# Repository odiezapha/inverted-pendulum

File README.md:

# Reaction Wheel Stabilized Inverted Pendulum
An inverted pendulum that maintains an upright attitude via reaction wheels. This repository
contains hardware and software development files. See the pdf for system equations.

Renderings:<br />

Simulation output:<br />
<br />

**Sim Test Conditions**<br />
Software: Python 3.6.4 on macOS High Sierra<br />
Computer: MacBook (Retina, 12-inch, Early 2015)<br />
Processor: 1.1 GHz Intel Core M<br />
RAM: 8 GB 1600 MHz DDR3<br />

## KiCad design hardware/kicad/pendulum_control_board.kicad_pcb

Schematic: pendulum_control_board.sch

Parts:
BT1, BT2: 1048; BAT_1048
C1, C4, C5, C7, C8, C10, C11, C12, C13, C14, C15, C16, C18, C19, C20, C21, C22, C23, C25, C26, C37, C41, C43, C47, C56, C64, C65, C66, C71, C72, C74, C75, C79, C82: 0.1uF; SPARKFUN-CAPACITORS_0603
C2, C57, C58, C59, C60, C61, C62, C63, C67, C68, C69, C70: 1.0uF; SPARKFUN-CAPACITORS_0603
C3, C6: 10uF; SPARKFUN-CAPACITORS_0603
C9, C28, C31, C32, C35: 10nF; SPARKFUN-CAPACITORS_0603
C17, C24, C49, C53: 1uF; SPARKFUN-CAPACITORS_0603
C27: 10uF; SPARKFUN-CAPACITORS_0805
C29, C33: 1nF; SPARKFUN-CAPACITORS_0603
C30, C34, C40, C46: 33nF; SPARKFUN-CAPACITORS_0603
C36, C39, C42, C45: 100uF; C_1206
C38, C44: 5.6nF; SPARKFUN-CAPACITORS_0603
C48, C51, C52, C55: 4.7uF; SPARKFUN-CAPACITORS_0603
C50, C54: 47nF; SPARKFUN-CAPACITORS_0603
C73, C76: 1.0uF; SPARKFUN-CAPACITORS_0805
C77: 10uF; SPARKFUN-CAPACITORS_1210
C78: 2.2uF; SPARKFUN-CAPACITORS_0603
C80, C81: 4.7pF; SPARKFUN-CAPACITORS_0603
D1, D17: MBR0520; SOD-123
D2: BAT54C; DIODE_SOT23
D3, D4, D16: 5973311402; SPARKFUN-LED_LED-1206
D5, D6: Yellow; SPARKFUN-LED_LED-0603
D7, D8, D9, D10: 15V; SPARKFUN-DISCRETESEMI_PANASONIC_SMINI2-F5-B
D11, D12, D13, D14: 1N4148; SOD-123
D15: QBLP677-RGB; SPARKFUN-LED_P-LCC-4-3
FB1, FB2, FB3: 30~/1.8A; SPARKFUN-COILS_0603
IC1: STM32F411CEU6; MICRO-STM_V3_UFQFPN48
IC2: LM358D; LINEAR_SO08
J1: DX07S024JJ2; TRISTAN+ROBITAILLE'S+LIBRARY_DX07S0224JJ2_USB-C
L1, L2: MSS1038-153ML; INDUCTOR-COILCRAFT_MSS1038
PAD1: T1-; WIREPAD_1_6_0_8
PAD2: T2-; WIREPAD_1_6_0_8
PAD3: T3-; WIREPAD_1_6_0_8
PAD4: T4-; WIREPAD_1_6_0_8
PAD5: T1+; WIREPAD_1_6_0_8
PAD6: T2+; WIREPAD_1_6_0_8
PAD7: T3+; WIREPAD_1_6_0_8
PAD8: T4+; WIREPAD_1_6_0_8
Q1, Q2, Q3, Q4: BSS138; BSS138_10_SOT23
Q5, Q6, Q7: 2N7002; TRANSISTOR-FET_SOT23
R1: 900K; SPARKFUN-RESISTORS_0603
R2, R5, R6, R9, R50, R63: 4.7K; SPARKFUN-RESISTORS_0603
R3, R4: 200K; SPARKFUN-RESISTORS_0603
R7, R8: 470; SPARKFUN-RESISTORS_0603
R10, R15, R17, R21, R25, R27, R28, R29, R30, R31, R34, R35, R38, R48, R66, R76, R89, R91, R102, R106: 10K; SPARKFUN-RESISTORS_0603
R11, R12, R13, R14, R19, R20, R23, R24: 68; SPARKFUN-RESISTORS_0603
R16, R18, R22, R26, R46, R100, R101: DNP; SPARKFUN-RESISTORS_0603
R32, R33, R36, R37, R51, R59, R64, R67, R70: 1K; SPARKFUN-RESISTORS_0603
R39, R52: 47K; SPARKFUN-RESISTORS_0603
R40, R53: 33K; SPARKFUN-RESISTORS_0603
R41, R54: 100; SPARKFUN-RESISTORS_0603
R42, R55, R61: 1.8K; SPARKFUN-RESISTORS_0603
R43, R56: 5.6K; SPARKFUN-RESISTORS_0603
R44, R57, R93, R94, R95, R96, R105: 100K; SPARKFUN-RESISTORS_0603
R45, R58: 0.3; SPARKFUN-RESISTORS_0603
R47, R65: 187K; SPARKFUN-RESISTORS_0603
R49, R62: 1M; SPARKFUN-RESISTORS_0603
R60, R68: 80; SPARKFUN-RESISTORS_0603
R69, R71, R73: 3K; SPARKFUN-RESISTORS_0603
R72: 140; SPARKFUN-RESISTORS_0603
R74: 4.5K; SPARKFUN-RESISTORS_0603
R75: 4.7; SPARKFUN-RESISTORS_0603
R77, R90, R92: 220; SPARKFUN-RESISTORS_0603
R78: 402K; SPARKFUN-RESISTORS_0603
R79: 107K; SPARKFUN-RESISTORS_0603
R80: SPARKFUN-RESISTORS_0603
R81, R82, R86, R87: 1; SPARKFUN-RESISTORS_0603
R83, R103, R104: 0; SPARKFUN-RESISTORS_0603
R84: 2K; SPARKFUN-RESISTORS_0603
R85: 115K; SPARKFUN-RESISTORS_0603
R88: 0.01; SPARKFUN-RESISTORS_0603
R97: 330; SPARKFUN-RESISTORS_0603
R98: 20; SPARKFUN-RESISTORS_0603
R99: 1m; R_1206
S1, S2: SPARKFUN-SWITCHES_SWITCH_SPST_SMD_A
S3: SW-SPST; SPARKFUN-SWITCHES_TACTILE_SWITCH_SMD_5.2MM
TP1, TP2, TP3, TP4, TP7: TP-040; KEYSTONE_TP-040
TP5, TP6: TP-040; SolderWirePad_single_2mmDrill
U1: FT231XS; SPARKFUN-IC-COMMS_SSOP20_L
U2, U3: V_REG_317SMD; SPARKFUN-IC-POWER_SOT223
U5: LTC6102DD; LINEAR-TECHNOLOGY_DFN8-3X3
U$1, U$7: L6235; L6234_SO24W
U$2, U$11: TPS61175; LIS3DE_HTSSOP14PWP
U$3: LIS3DE; LIS3DE_LGA-16
U$4: L3GD20H; LIS3DE_LGA-16
U$5: AD7280A; LIS3DE_LQFP48_N
U$6: TUSB320LAI; LIS3DE_X2QFN-12
U$8: ITS13FV2SR; LIS3DE_ITS13FV2SR
U$9, U$13: SS3P6L; LIS3DE_TO-277A
U$10: ISL9238; LIS3DE_TQFN-32
U$12: WE-SD; LIS3DE_ROD-CORE-CHOKE
U$14, U$15, U$16, U$17: EPC2023; LIS3DE_EPC2023
U$18: SI7655DN; LIS3DE_POWERPAK-1212-8S
X1, X2: 5566-8; CON-MOLEX_5566-8
Y2: 32.768kHz; SPARKFUN-CLOCKS_CRYSTAL-SMD-3.2X1.5MM

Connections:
/3P3V: C3.2, C4.2, C5.2, C6.2, C8.1, C10.2, C57.1, C72.2, C73.1, D5.A, D6.A, IC1.9 (VDDA), IC1.24 (VDD), IC1.36 (VDD), IC1.48 (VDD), R3.1, R4.2, R5.2, R6.2, R61.2, R72.1, R76.2, R77.2, R89.2, R90.2, R91.2, R92.2, R93.2, R95.2, R106.2, TP5.1, U1.3 (VCCIO), U1.13 (3V3OUT), U2.2 (OUT), U$3.1 (VDD_IO), U$3.14 (VDD), U$4.1 (VDD_IO), U$4.16 (VDD), U$5.29 (VDRIVE), U$6.12 (VDD)
/5V: C2.1, C74.1, IC2.8 (V+), R70.2, TP6.1, U3.2 (OUT), U5.3 (V-/EN), U5.7 (V+), X1.3, X2.3
/ACOK: Q5.1 (G), R76.1, U$10.24 (ACOK)
/ALERT_BATT: IC1.40 (PB4), U$5.27 (ALERT)
/AUX_TERM: R102.2, U$5.32 (AUX_TERM)
/BATGONE: S2.2, U$10.25 (BATGONE)
/BOOT0: IC1.44 (BOOT0), R105.2, TP7.1
/BRAKE_X: IC1.45 (PB8), U$1.14 (BRAKE)
/BRAKE_Y: IC1.12 (PA2), U$7.14 (BRAKE)
/CB1: R15.1, U$5.12 (CB1)
/CB2: R17.1, U$5.10 (CB2)
/CB3: R21.1, U$5.8 (CB3)
/CB4: R25.1, U$5.6 (CB4)
/CC1: J1.A5 (CC1), U$6.1 (CC1)
/CC2: J1.B5 (CC2), U$6.2 (CC2)
/CLK: IC1.25 (PB12), U$3.4 (SCL/SPC), U$4.2 (SCL/SPC), U$5.22 (SCLK)
/CREF: C25.1, U$5.39 (CREF)
/CSON: C68.2, C69.1, R87.1, U$10.1 (CSON)
/CSOP: C68.1, C70.1, R86.1, U$10.2 (CSOP)
/CS_ACCEL: IC1.15 (PA5), U$3.8 (CS)
/CS_BATT: IC1.29 (PA8), U$5.21 (CS)
/CS_GYRO: IC1.21 (PB10), U$4.5 (CS)
/DEN_GYRO: IC1.18 (PB0), U$4.8 (DEN)
/DM: J1.A7 (D-), J1.B7 (D-), U1.12 (USBDM)
/DP: J1.A6 (D+), J1.B6 (D+), U1.11 (USBDP)
/DRDY/INT2_GYRO: IC1.20 (PB2), U$4.6 (DRDY/INT2)
/EN_BLU_L: D15.3 (BLU), IC1.34 (PA13)
/EN_GRN_L: D15.2 (GRN), IC1.37 (PA14)
/EN_RED_H: IC1.38 (PA15), R74.1
/EN_RED_L: IC1.39 (PB3), R73.2
/EN_WHEEL: IC1.10 (PA0-WKUP), R44.2, R57.2
/FWD/REV_X: IC1.46 (PB9), U$1.11 (FWD/REV)
/FWD/REV_Y: IC1.11 (PA1), U$7.11 (FWD/REV)
/HALL1_X: U$1.1 (H1), X1.1
/HALL1_Y: U$7.1 (H1), X2.1
/HALL2_X: U$1.23 (H2), X1.2
/HALL2_Y: U$7.23 (H2), X2.2
/HALL3_X: U$1.24 (H3), X1.5
/HALL3_Y: U$7.24 (H3), X2.5
/INT1_ACCEL: IC1.13 (PA3), U$3.11 (INT1)
/INT1_GRYO: IC1.19 (PB1), U$4.7 (INT1)
/INT2_ACCEL: IC1.14 (PA4), U$3.9 (INT2)
/I_BATT: IC1.3 (PC14), R100.2, U5.4 (OUT)
/MISO: IC1.16 (PA6), U$3.7 (SDO/SA0), U$4.4 (SDO/SA0), U$5.26 (SDO)
/MOSI: IC1.17 (PA7), U$3.6 (SDO/SDI/SDA), U$4.3 (SDA/SDI/SDO), U$5.23 (SDI)
/N$1: R2.1, U$6.3 (PORT)
/N$2: R8.1, U1.10 (CBUS2)
/N$3: R4.1, U$6.6 (INT_N/OUT3)
/N$4: D5.C, R8.2
/N$5: R7.1, U1.17 (CBUS1)
/N$6: R1.2, U$6.4 (VBUS_DET)
/N$7: D6.C, R7.2
/N$8: C9.2, U$4.14 (CAP)
/N$9: D7.C, Q1.1 (G), R15.2, R16.2
/N$10: R9.1, R10.2, U1.19 (CBUS3)
/N$11: R3.2, U$6.9 (ID)
/N$12: D8.C, Q2.1 (G), R17.2, R18.2
/N$13: C11.1, C12.2, C19.1, R28.2, U$5.11 (VIN1)
/N$14: C7.1, U1.14 (~RESET)
/N$15: Q1.3 (D), R13.1, R14.1
/N$16: C33.1, R40.2, U$1.4 (RCOFF)
/N$17: C78.1, IC1.22 (VCAP1)
/N$18: IC1.6 (OSC_OUT), R103.1
/N$19: R38.2, U$5.14 (MASTER)
/N$20: Q2.3 (D), R11.1, R12.1
/N$21: D9.C, Q3.1 (G), R21.2, R22.2
/N$22: Q3.3 (D), R19.1, R20.1
/N$23: D10.C, Q4.1 (G), R25.2, R26.2
/N$24: Q4.3 (D), R23.1, R24.1
/N$25: C31.2, R39.2, U$1.9 (RCPULSE)
/N$26: C29.1, R53.2, U$7.4 (RCOFF)
/N$27: R37.2, U$5.25 (SDO_IO)
/N$28: C13.1, C14.2, C20.1, R30.2, U$5.7 (VIN3)
/N$29: C11.2, C18.1, R27.2, U$5.13 (VIN0)
/N$30: C14.1, C22.1, R31.2, U$5.5 (VIN4)
/N$31: C12.1, C13.2, C21.1, R29.2, U$5.9 (VIN2)
/N$32: R33.2, U$5.43 (SDI_HI)
/N$33: R32.2, U$5.42 (ALERT_HI)
/N$34: R36.2, U$5.28 (ALERT_IO)
/N$35: C28.2, R52.2, U$7.9 (RCPULSE)
/N$36: R35.1, U$5.34 (AUX5)
/N$37: R34.1, U$5.33 (AUX6)
/N$38: C38.1, R44.1, U$1.2 (DIAG), U$1.12 (EN)
/N$39: C40.2, IC2.2 (-IN), R49.2, R50.1
/N$40: C44.1, R57.1, U$7.2 (DIAG), U$7.12 (EN)
/N$41: R51.2, R64.2
/N$42: C40.1, IC2.1 (OUT), R43.2, R49.1
/N$43: R58.1, U$7.3 (SENSEA), U$7.10 (SENSEB)
/N$44: R45.1, U$1.3 (SENSEA), U$1.10 (SENSEB)
/N$45: C45.1, D13.1 (K), U$7.15 (VBOOT)
/N$47: C39.1, D11.1 (K), U$1.15 (VBOOT)
/N$49: C35.1, R41.1
/N$50: C35.2, U$1.22 (VCP)
/N$51: C32.1, R54.1
/N$52: C32.2, U$7.22 (VCP)
/N$53: L1.2, U$2.1 (SW), U$2.2 (SW), U$9.PIN1 (A), U$9.PIN2 (A)
/N$54: C53.2, U$11.8 (COMP)
/N$55: R60.2, U$11.10 (FREQ)
/N$56: C46.2, IC2.6 (-IN), R62.2, R63.1
/N$57: C54.1, U$11.5 (SS)
/N$58: C53.1, R59.2
/N$59: R47.1, R48.2, U$11.9 (FB)
/N$60: L2.2, U$11.1 (SW), U$11.2 (SW), U$13.PIN1 (A), U$13.PIN2 (A)
/N$61: C46.1, IC2.7 (OUT), R56.2, R62.1
/N$62: C62.2, D1.1 (K), U$10.10 (PHASE1), U$10.12 (BOOT1), U$12.P$1 (1), U$14.2 (S), U$14.5 (S), U$14.6 (S), U$14.9 (S), U$14.10 (S), U$14.13 (S), U$14.14 (S), U$14.17 (S), U$14.18 (S), U$14.21 (S), U$14.22 (S), U$14.25 (S), U$14.26 (S), U$14.29 (S), U$15.3 (D), U$15.4 (D), U$15.7 (D), U$15.8 (D), U$15.11 (D), U$15.12 (D), U$15.15 (D), U$15.16 (D), U$15.19 (D), U$15.20 (D), U$15.23 (D), U$15.24 (D), U$15.27 (D), U$15.28 (D)
/N$63: D15.4 (A), R72.2
/N$64: R70.1, R71.2, U3.1 (ADJ)
/N$65: C63.1, D17.1 (K), U$10.4 (BOOT2), U$10.6 (PHASE2), U$12.P$2 (4), U$16.2 (S), U$16.5 (S), U$16.6 (S), U$16.9 (S), U$16.10 (S), U$16.13 (S), U$16.14 (S), U$16.17 (S), U$16.18 (S), U$16.21 (S), U$16.22 (S), U$16.25 (S), U$16.26 (S), U$16.29 (S), U$17.3 (D), U$17.4 (D), U$17.7 (D), U$17.8 (D), U$17.11 (D), U$17.12 (D), U$17.15 (D), U$17.16 (D), U$17.19 (D), U$17.20 (D), U$17.23 (D), U$17.24 (D), U$17.27 (D), U$17.28 (D)
/N$66: C49.2, U$2.8 (COMP)
/N$67: R68.2, U$2.10 (FREQ)
/N$68: C50.1, U$2.5 (SS)
/N$69: C49.1, R67.2
/N$70: R61.1, R69.2, U2.1 (ADJ)
/N$71: R65.1, R66.2, U$2.9 (FB)
/N$72: C67.1, R84.2
/N$73: R83.2, U$10.29 (AMON/BMON)
/N$74: D15.1 (RED), R73.1, R74.2
/N$75: IC1.5 (OSC_IN), R104.1
/N$76: C80.1, R103.2, Y2.P$2 (2)
/N$77: C81.2, R104.2, Y2.P$1 (1)
/N$79: C59.1, R75.1, U$10.18 (VDD)
/N$80: D3.C, Q5.3 (D)
/N$81: C58.1, R83.1
/N$82: D3.A, R77.1
/N$83: U$10.32 (BGATE), U$18.4 (G)
/N$85: R98.2, U5.1 (-INS), U5.2 (-INF)
/N$86: R93.1, S2.3 (S)
/N$87: R94.2, S2.1 (O)
/N$88: D4.C, Q6.3 (D)
/N$89: D4.A, R90.1
/N$91: C64.1, C65.1, R82.2, U$10.14 (CSIN)
/N$92: C64.2, C66.2, R81.2, U$10.15 (CSIP)
/N$94: R80.1, R82.1, TP4.1, U$14.3 (D), U$14.4 (D), U$14.7 (D), U$14.8 (D), U$14.11 (D), U$14.12 (D), U$14.15 (D), U$14.16 (D), U$14.19 (D), U$14.20 (D), U$14.23 (D), U$14.24 (D), U$14.27 (D), U$14.28 (D)
/N$95: D16.C, Q7.3 (D)
/N$96: D16.A, R92.1
/N$98: R95.1, S1.3 (S)
/N$99: C61.2, R78.1, R79.2, U$10.19 (ACIN)
/N$100: R96.2, S1.1 (O)
/N$101: R97.1, U$8.L2
/N$107: D2.3 (CC), U$10.17 (DCIN)
/N$108: R84.1, U$10.28 (COMP)
/N$109: U$10.9 (LGATE1), U$15.1 (G)
/N$110: R85.1, U$10.27 (PROG)
/N$111: U$10.11 (UGATE1), U$14.1 (G)
/N$116: C74.2, U5.6 (VREG)
/N$117: U$10.7 (LGATE2), U$17.1 (G)
/N$118: U$10.5 (UGATE2), U$16.1 (G)
/OTGEN/CMIN: S1.2, U$10.20 (OTGEN/CMIN)
/OTGPG/CMOUT: Q7.1 (G), R91.1, U$10.26 (OTGPG/CMOUT)
/OUT1_X: U$1.5 (OUT1), X1.7
/OUT1_Y: U$7.5 (OUT1), X2.7
/OUT2_X: U$1.21 (OUT2), X1.8
/OUT2_Y: U$7.21 (OUT2), X2.8
/OUT3_X: U$1.16 (OUT3), X1.4
/OUT3_Y: U$7.16 (OUT3), X2.4
/PD_BATT: IC1.41 (PB5), U$5.15 (PD)
/PROCHOT: Q6.1 (G), R89.1, U$10.23 (PROCHOT)
/PSYS: IC1.2 (PC13), U$10.30 (PSYS)
/RST: C71.1, C82.2, IC1.7 (NRST), S3.1, S3.2 (1)
/SCL: IC1.42 (PB6), R6.1, U$6.8 (SCL/OUT2), U$10.22 (SCL)
/SDA: IC1.43 (PB7), R5.1, U$6.7 (SDA/OUT1), U$10.21 (SDA)
/SW1: C79.2, IC1.27 (PB14), R106.1, U$8.1, U$8.2
/SW_LED_GH_RL: IC1.26 (PB13), U$8.L1
/SW_LED_RH_GL: IC1.28 (PB15), R97.2
/TACHO_X: R50.2, R51.1, U$1.8 (TACHO)
/TACHO_Y: R63.2, R64.1, U$7.8 (TACHO)
/T_CELL1: PAD5.1, U$5.38 (AUX1)
/T_CELL2: PAD6.1, U$5.37 (AUX2)
/T_CELL3: PAD7.1, U$5.36 (AUX3)
/T_CELL4: PAD8.1, U$5.35 (AUX4)
/UART_CTS: IC1.32 (PA11), U1.9 (~CTS)
/UART_RTS: IC1.33 (PA12), U1.2 (~RTS)
/UART_RXD: IC1.31 (PA10), U1.20 (TXD)
/UART_TXD: IC1.30 (PA9), U1.4 (RXD)
/VDDP: C60.1, R75.2, U$10.8 (VDDP)
/VDD_BATT: C15.1, C27.1, FB1.1, R32.1, R33.1, R38.1, U$5.16 (VDD), U$5.44 (CNVST_HI), U$5.45 (SDO_HI), U$5.46 (SCLK_HI), U$5.47 (CS_HI), U$5.48 (PD_HI)
/VREF: C24.1, C41.1, C47.1, IC2.3 (+IN), IC2.5 (+IN), U$5.40 (VREF)
/VREF_X: C34.2, R42.2, R43.1, U$1.13 (VREF)
/VREF_Y: C30.2, R55.2, R56.1, U$7.13 (VREF)
/VSYS+: C75.1, C76.1, C77.1, D2.2 (A2), R86.2, R88.2, TP1.1, U$10.3 (VSYS), U$16.3 (D), U$16.4 (D), U$16.7 (D), U$16.8 (D), U$16.11 (D), U$16.12 (D), U$16.15 (D), U$16.16 (D), U$16.19 (D), U$16.20 (D), U$16.23 (D), U$16.24 (D), U$16.27 (D), U$16.28 (D)
/VSYS-: R87.2, R88.1, TP2.1, U$18.1 (S), U$18.2 (S), U$18.3 (S)
/V_BATT: C1.2, C48.2, C52.2, C56.2, L1.1, L2.1, R98.1, R99.2, U2.3 (IN), U3.3 (IN), U$2.3 (VIN), U$2.4 (EN), U$10.31 (VBAT), U$11.3 (VIN), U$11.4 (EN), U$18.5 (D), U$18.6 (D), U$18.7 (D), U$18.8 (D), U$18.P (D)
/V_BUS: D2.1 (A1), J1.A4 (V+), J1.A9 (V+), J1.B4 (V+), J1.B9 (V+), R1.1, R9.2, R78.2, R80.2, R81.1, TP3.1, U1.15 (VCC), U$10.16 (ADP)
/V_CELL1: BT1.C1-, BT1.C2+, D8.A, IC1.1 (VBAT), Q2.2 (S), R13.2, R14.2, R18.1, R28.1
/V_CELL2: BT1.C1+, BT2.C2-, D9.A, Q3.2 (S), R11.2, R12.2, R22.1, R29.1
/V_CELL3: BT2.C1-, BT2.C2+, D10.A, Q4.2 (S), R19.2, R20.2, R26.1, R30.1
/V_CELL4: BT2.C1+, C26.1, FB1.2, R23.2, R24.2, R31.1, R99.1, U5.8 (+IN)
/V_DRIVER_X: C36.2, C37.2, C39.2, C51.1, D12.2 (A), R65.2, U$1.17 (VSB), U$1.20 (VSA), U$9.PIN3 (C)
/V_DRIVER_Y: C42.2, C43.2, C45.2, C55.1, D14.2 (A), R47.2, U$7.17 (VSB), U$7.20 (VSA), U$13.PIN3 (C)
/V_REG_BATT: C16.1, C17.1, C23.1, PAD1.1, PAD2.1, PAD3.1, PAD4.1, R34.2, R35.2, U$5.18 (VREG), U$5.19 (DVCC), U$5.24 (CNVST), U$5.30 (AVCC)
GND: BT1.C2-, C1.1, C2.2, C3.1, C4.1, C5.1, C6.1, C7.2, C8.2, C9.1, C10.1, C15.2, C16.2, C17.2, C18.2, C19.2, C20.2, C21.2, C22.2, C23.2, C24.2, C25.2, C26.2, C27.2, C28.1, C29.2, C30.1, C31.1, C33.2, C34.1, C36.1, C37.1, C38.2, C41.2, C42.1, C43.1, C44.2, C47.2, C50.2, C54.2, C56.1, C57.2, C58.2, C59.2, C60.2, C61.1, C62.1, C63.2, C65.2, C66.1, C67.2, C69.2, C70.2, C71.2, C72.1, C73.2, C75.2, C76.2, C77.2, C78.2, C79.1, C80.2, C81.1, C82.1, D1.2 (A), D7.A, D17.2 (A), FB2.2, FB3.2, IC1.8 (VSSA), IC1.23 (VSS), IC1.35 (VSS), IC1.47 (VSS), IC2.4 (V-), J1.A1 (GND), J1.A12 (GND), J1.B1 (GND), J1.B12 (GND), J1.SHIE (SHIELD), Q1.2 (S), Q5.2 (S), Q6.2 (S), Q7.2 (S), R2.2, R10.1, R16.1, R27.1, R36.1, R37.1, R39.1, R40.1, R42.1, R45.2, R46.1, R48.1, R52.1, R53.1, R55.1, R58.2, R59.1, R60.1, R66.1, R67.1, R68.1, R69.1, R71.1, R79.1, R85.2, R94.1, R96.1, R100.1, R101.1, R102.1, R105.1, S3.3 (2), S3.4 (2), U1.6 (GND), U1.16 (GND), U5.5 (V-), U$1.6 (GND), U$1.7 (GND), U$1.18 (GND), U$1.19 (GND), U$2.6 (SYNC), U$2.7 (AGND), U$2.11 (NC), U$3.5 (GND), U$3.10 (RES), U$3.12 (GND), U$4.9 (RES), U$4.10 (RES), U$4.11 (RES), U$4.12 (GND), U$4.13 (GND), U$4.15 (RES), U$5.17 (VSS), U$5.20 (DGND), U$5.31 (AGND), U$5.41 (REFGND), U$6.5 (ADDR), U$6.10 (GND), U$6.11 (EN_N), U$7.6 (GND), U$7.7 (GND), U$7.18 (GND), U$7.19 (GND), U$8.3, U$8.4, U$10.GND, U$11.6 (SYNC), U$11.7 (AGND), U$11.11 (NC), U$15.2 (S), U$15.5 (S), U$15.6 (S), U$15.9 (S), U$15.10 (S), U$15.13 (S), U$15.14 (S), U$15.17 (S), U$15.18 (S), U$15.21 (S), U$15.22 (S), U$15.25 (S), U$15.26 (S), U$15.29 (S), U$17.2 (S), U$17.5 (S), U$17.6 (S), U$17.9 (S), U$17.10 (S), U$17.13 (S), U$17.14 (S), U$17.17 (S), U$17.18 (S), U$17.21 (S), U$17.22 (S), U$17.25 (S), U$17.26 (S), U$17.29 (S), X1.6, X2.6
GNDPWR: C48.1, C51.2, C52.1, C55.2, FB2.1, FB3.1, R46.2, R101.2, U$2.12 (PGND), U$2.13 (PGND), U$2.14 (PGND), U$2.EXP (PGND), U$11.12 (PGND), U$11.13 (PGND), U$11.14 (PGND), U$11.EXP (PGND)
unnamed: D11.2 (A), D12.1 (K), R41.2
unnamed: D13.2 (A), D14.1 (K), R54.2

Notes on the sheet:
REV2: Replace with USART part
NOTE: 80 Ohm resistor sets FREQ to 1200 kHz, 187 KOhm sets V_DRIVER close to 24 V
QUESTION: Do I need DTR, DSR, DCR, and RI connected to the micro?
#TODO: Get resistor values double checked
NOTE: Max Vf for RED is 2.5 V
NOTE: Is this okay to interface with the 3.3V micro?
NOTE: Battery cells are INR18650-25R
Motor Drive
Battery Charging and Monitoring
Sensing
NOTE: C78 needs to be low ESR
NOTE: Motors are Maxon EC 45 flat 70 Watt (PN: 397172)

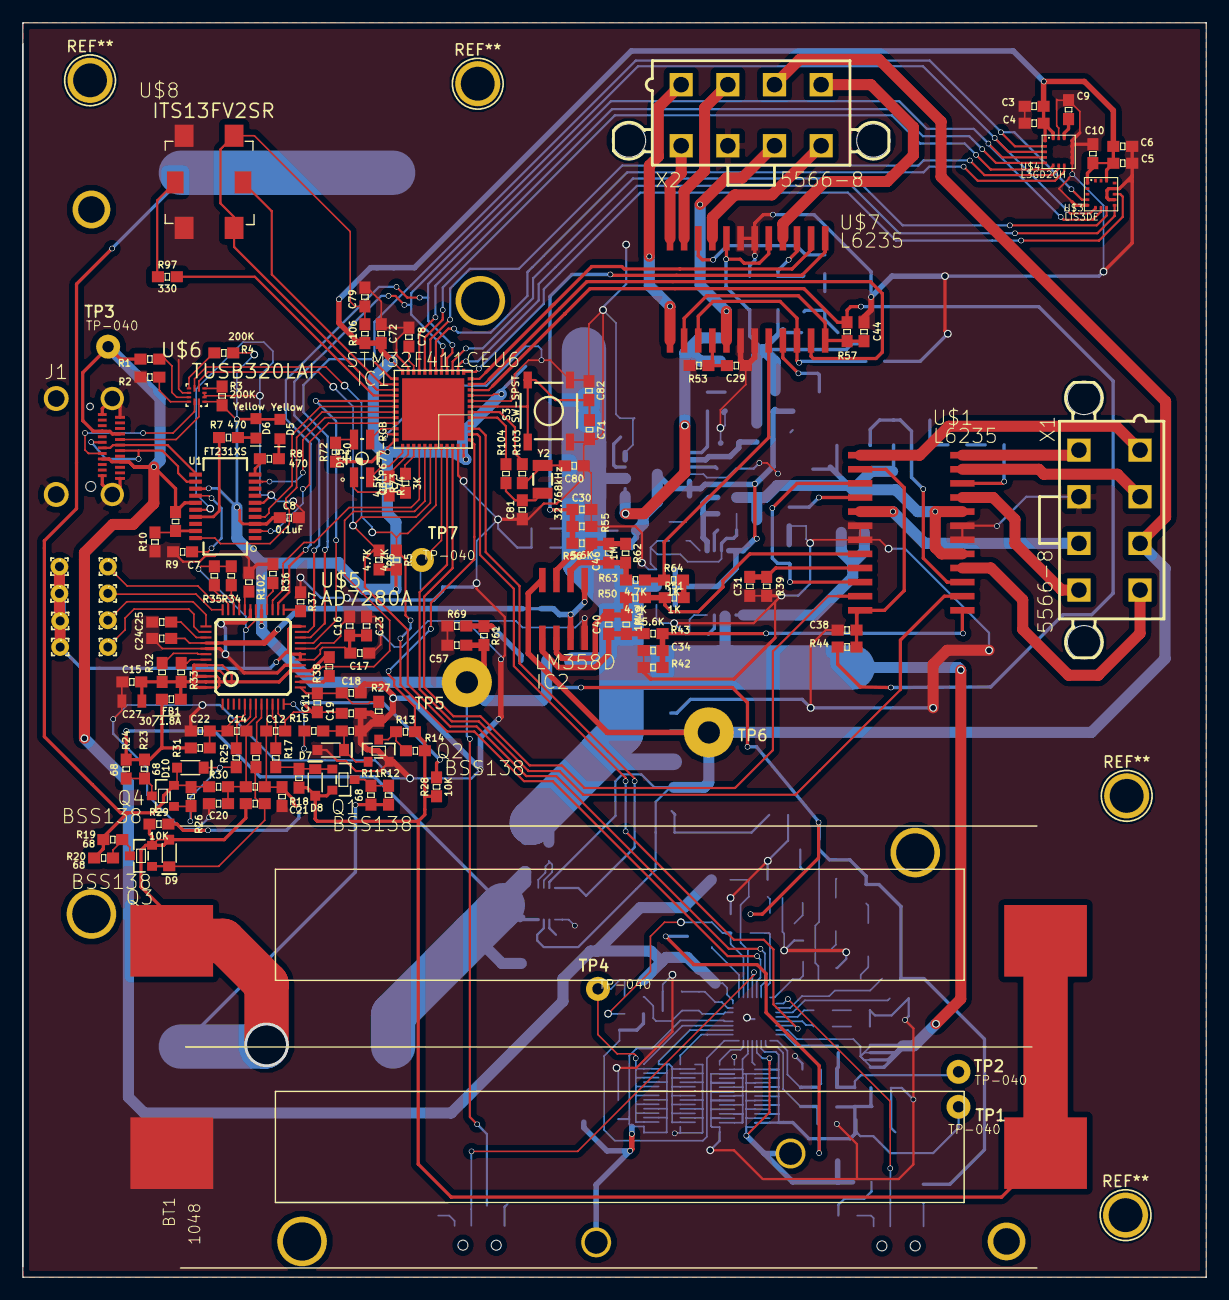
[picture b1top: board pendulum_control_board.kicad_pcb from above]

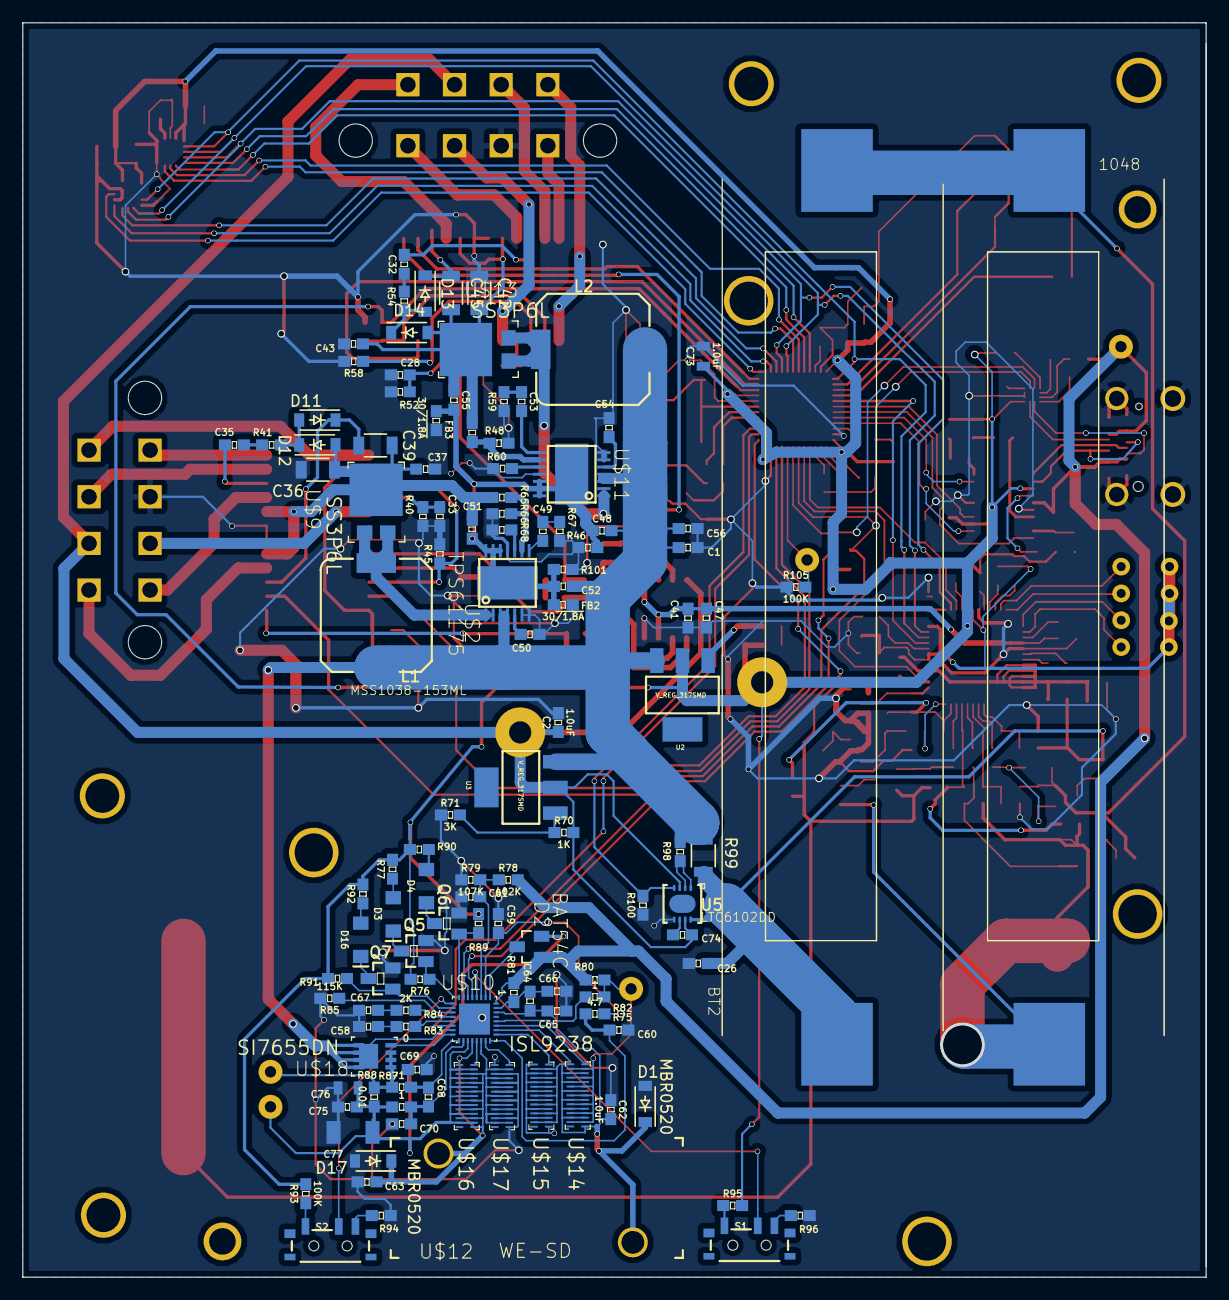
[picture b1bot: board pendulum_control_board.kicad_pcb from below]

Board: 2 copper layers, 106.5 x 112.9 mm, 265 parts (120 on the bottom side), 194 nets.

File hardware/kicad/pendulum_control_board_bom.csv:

Item,Quantity Per PCB,Manufacturer PN,Manufacturer,Supplier PN,Supplier,Unit Price,Footprint,Value,References
1,34,CGA3E2X7R1E104K080AA,TDK Corporation,445-5667-1-ND,digikey,0.063,603,0.1uF,C1 C4 C5 C7 C8 C10 C11 C12 C13 C14 C15 C16 C18 C19 C20 C21 C22 C23 C25 C26 C37 C41  C43 C47 C56 C64 C65 C66 C71 C72 C74 C75 C79 C82 
2,18,TMK107BJ105KA-T,Taiyo Yuden,587-1248-1-ND,digikey,0.06,603,1.0uF,C2 C17 C24 C49 C53 C57 C58 C59 C60 C61 C62 C63 C67 C68 C69 C70 C73 C76
3,4,GRM31CD80J107ME39L,Murata Electronics North America,490-10525-1-ND,digikey,0.57,1206,100uF,C36 C39 C42 C45
4,7,C0603C103J3GACTU,KEMET,399-7838-1-ND,digikey,0.33,603,10nF,C3 C6 C9 C28 C31 C32 C35
5,1,C0805C103J3GACTU,KEMET,399-7990-1-ND,digikey,0.034,805,10uF,C27
6,1,1210D103J250KHT,Knowles Novacap,1763-1060-1-ND,digikey,4.91,1210,10uF,C77
7,2,C0603C102F3GACTU,KEMET,399-7825-1-ND,digikey,0.29,603,1nF,C29 C33
8,1,EMK107BJ225KA-T,Taiyo Yuden,587-1430-1-ND,digikey,0.12,603,2.2uF,C78
9,2,CL10B333KA8NNNC,Samsung Electro-Mechanics,1276-2038-1-ND,digikey,0.1,603,33nF,C30 C34 C40 C46
10,2,C0603C479D3GAC7867,KEMET,399-15411-1-ND,digikey,0.29,603,4.7pF,C80 C81
11,4,C0603C472F3GACTU,KEMET,399-9087-1-ND,digikey,1.15,603,4.7uF,C48 C51 C52 C55
12,2,CL10B473KA8NFNC,Samsung Electro-Mechanics,1276-2072-1-ND,digikey,0.1,603,47nF,C50 C54
13,2,C0603C562K3RAC7867,KEMET,399-15415-6-ND,digikey,0.29,603,5.6nF,C38 C44
14,4,DZ2J150M0L,Panasonic Electronics Components,DZ2J150M0LCT-ND,digikey,0.21,SMINI2-F5-B,15V,D7 D8 D9 D10
15,4,1N4148W-7-F,Diodes Incorporated,1N4148W-FDICT-ND,digikey,0.18,SOD-123,1N4148,D11 D12 D13 D14
16,3,5973311402NF,Dialight,350-3771-ND,digikey,0.82,1206,5973311402,D3 D4 D16
17,1,BAT54C RFG,Taiwan Semiconductor Corporation,BAT54CRFGCT-ND,digikey,0.25,DIODE_SOT23,BAT54C,D2
18,2,MBR0520-TP,Micro Commercial Co,MBR0520TPMSCT-ND,digikey,0.41,SOD-123,MBR0520,D1 D17
19,1,QBLP677-RGB (HIGH BRIGHT),QT Brighttek QTB,1516-1195-1-ND,digikey,0.89,4-PLCC,QBLP677-RGB,D15
20,2,LTST-C191KSKT,Lite-On Inc,160-1448-1-ND,digikey,0.31,603,Yellow,D5 D6
21,3,742792651,Wurth Electronics Inc,732-1593-1-ND,digikey,0.17,603,30~/1.8A,FB1 FB2 FB3
22,1,LM358DT,STMicroelectronics,497-1591-1-ND,digikey,0.43,SO08,LM358D,IC2
23,1,STM32F401CBU6,STMicroelectronics,497-17425-ND,digikey,4.98,UFQFPN48,STM32F411CEU6,IC1
24,1,DX07S024JJ2R1300,JAE Electronics,670-2794-1-ND,digikey,2.61,,DX07S024JJ2,J1
25,2,MSS1038-153MLC,Coilcraft,994-MSS1038-153MLC,mouser,1.73,INDUCTOR-COILCRAFT_MSS1038,MSS1038-153ML,L1 L2
26,3,2N7002H-7,Diodes Incorporated,2N7002H-7DICT-ND,digikey,0.3,SOT23,2N7002,Q5 Q6 Q7
27,4,"BSS138P,215",Nexperia USA Inc.,1727-1142-1-ND,digikey,0.28,SOT23,BSS138,Q1 Q2 Q3 Q4
28,3,RC0603JR-070RL,Yageo,311-0.0GRCT-ND,digikey,0.1,603,0,R83 R103 R104
29,1,PMR03EZPFU10L0,Rohm Semiconductor,RHM0.01BVCT-ND,digikey,0.69,603,0.01,R88
30,1,WSL0603R0200FEA,Vishay Dale,WSLJ-.02CT-ND,digikey,0.84,603,0.02,R80
31,2,UCR03EWPFSR030,Rohm Semiconductor,RHM1268CT-ND,digikey,0.58,603,0.3,R45 R58
32,4,ERJ-3RQF1R0V,Panasonic Electronics Components,P1.0AJCT-ND,digikey,0.17,603,1,R81 R82 R86 R87
33,3,MCT06030C1801FP500,Vishay Beyschlag,MCT0603-1.80K-CFCT-ND,digikey,0.18,603,1.8K,R42 R55 R61
34,2,ERA-3AEB101V,Panasonic Electronics Components,P100DBCT-ND,digikey,0.35,603,100,R41 R54
35,7,RT0603BRD07100KL,Yageo,YAG1235CT-ND,digikey,0.35,603,100K,R44 R57 R93 R94 R95 R96 R105
36,20,MCT06030C1002FP500,Vishay Beyschlag,MCT0603-10.0K-CFCT-ND,digikey,0.152,603,10K,R10 R15 R17 R21 R25 R27 R28 R29 R30 R31 R34 R35 R38 R48 R66 R76 R89 R91 R102 R106
37,1,ERA-3AEB1073V,Panasonic Electronics Components,P107KDBCT-ND,digikey,0.35,603,107K ,R79 
38,1,ERA-3AEB1153V,Panasonic Electronics Components,P115KDBCT-ND,digikey,0.35,603,115K,R85  
39,1,ERA-3AEB1400V,Panasonic Electronics Components,P140DBCT-ND,digikey,0.35,603,140,R72
40,2,ERA-3AEB1873V,Panasonic Electronics Components,P187KDBCT-ND,digikey,0.35,603,187K,R47 R65
41,9,ERA-3AEB102V,Panasonic Electronics Components,P1.0KDBCT-ND,digikey,0.35,603,1K,R32 R33 R36 R37 R51 R59 R64 R67 R70
42,1,CSR1206-0R001F1,Riedon,696-1369-1-ND,digikey,0.59,1206,1m,R99
43,2,CPF0603B1M0E,TE Connectivity Passive Product,A119955CT-ND,digikey,0.52,603,1M,R49 R62
44,1,ERA-3AEB202V,Panasonic Electronics Components,P2.0KDBCT-ND,digikey,0.35,603,2K ,R84 
45,1,ESR03EZPJ200,Rohm Semiconductor,RHM20DCT-ND,digikey,0.1,603,20,R98
46,2,ERA-3AEB204V,Panasonic Electronics Components,P200KDBCT-ND,digikey,0.35,603,200K,R3 R4
47,3,ESR03EZPJ221,Rohm Semiconductor,RHM220DCT-ND,digikey,0.1,603,220,R77 R90 R92
48,1,RC0603FR-07330RL,Yageo,311-330HRCT-ND,digikey,0.1,603,330,R97
49,2,ERA-3AEB333V,Panasonic Electronics Components,P33KDBCT-ND,digikey,0.35,603,33K,R40 R53
50,3,ERA-3AEB302V,Panasonic Electronics Components,P3.0KDBCT-ND,digikey,0.35,603,3K,R69 R71 R73
51,1,ERA-3AEB4531V,Panasonic Electronics Components,P4.53KDBCT-ND,digikey,0.35,603,4.5K,R74
52,1,RNCP0603FTD4R70,Stackpole Electronics Inc,RNCP0603FTD4R70CT-ND,digikey,0.1,603,4.7,R75
53,6,ERA-3AEB472V,Panasonic Electronics Components,P4.7KDBCT-ND,digikey,0.35,603,4.7K,R2 R5 R6 R9 R50 R63
54,1,RC0603FR-07402KL,Yageo,311-402KHRCT-ND,digikey,0.1,603,402K,R78  
55,2,MCT06030C4700FP500,Vishay Beyschlag,MCT0603-470-CFCT-ND,digikey,0.18,603,470,R7 R8
56,2,ERA-3AEB473V,Panasonic Electronics Components,P47KDBCT-ND,digikey,0.35,603,47K,R39 R52
57,2,ESR03EZPJ562,Rohm Semiconductor,RHM5.6KDCT-ND,digikey,0.1,603,5.6K,R43 R56
58,8,ESR03EZPJ680,Rohm Semiconductor,RHM68DCT-ND,digikey,0.1,603,68,R11 R12 R13 R14 R19 R20 R23 R24
59,2,RC0603FR-0780R6L,Yageo,311-80.6HRCT-ND,digikey,0.1,603,80,R60 R68
60,1,RC0603FR-07909KL,Yageo,311-909KHRCT-ND,digikey,0.1,603,900K,R1
61,7,Resistor (DNP),,DNP,,,603,DNP,R16 R18 R22 R26 R46 R100 R101
62,1,RS-187R05A2-DS MT RT (DNP),C&K,CKN10361CT-ND,digikey,0.53,SW-SPST,DNP,S3
63,2,CUS-12TB (DNP),Nidec Copal Electronics,563-1102-1-ND,digikey,0.71,"Surface Mount, Right Angle",DNP,S1 S2
64,1,AD7280AWBSTZ,Analog Devices Inc,AD7280AWBSTZ-ND,digikey,10.65,LQFP48_N,AD7280A,U$5
65,4,EPC2023,EPC,917-1088-1-ND,digikey,8.21,EPC2023,EPC2023,U$14 U$15 U$16 U$17
66,1,FT231XS-R,FTDI,768-1129-1-ND,digikey,2.12,SSOP20_L,FT231XS,U1
67,1,ISL9238HRTZ-T7A,Intersil,ISL9238HRTZ-T7ACT-ND,digikey,8.78,TQFN-32,ISL9238,U$10
68,1,ITS13FV2SR,C&K,CKN10459CT-ND,digikey,4.58,ITS13FV2SR,ITS13FV2SR,U$8
69,1,L3GD20HTR,STMicroelectronics,497-13931-1-ND,digikey,3.42,LGA-16,L3GD20H,U$4
70,2,L6235D013TR,STMicroelectronics,497-4009-1-ND,digikey,7.33,SO24W,L6235,U$1 U$7
71,1,LIS3DETR,STMicroelectronics,497-16262-1-ND,digikey,1.36,LGA-16,LIS3DE,U$3
72,1,LTC6102IDD#PBF,Linear Technology/Analog devices,LTC6102IDD#PBF-ND,digikey,4.07,DFN8-3X3,LTC6102DD,U5
73,1,SI7655DN-T1-GE3,Vishay/Siliconix,78-SI7655DN-T1-GE3,mouser,1.65,POWERPAK-1212-8S,SI7655DN,U$18
74,2,SS5P6-M3/86A,Vishay Semiconductor Diodes,SS5P6-M3/86AGICT-ND,digikey,0.65,TO-277A,SS3P6L,U$9 U$13
75,2,TPS61175PWPR,Texas Instruments,296-24013-1-ND,digikey,3.12,HTSSOP14PWP,TPS61175,U$2 U$11
76,1,TUSB320LAIRWBR,Texas Instruments,595-TUSB320LAIRWBR,digikey,1.82,X2QFN-12,TUSB320LAI,U$6
77,2,MIC5201-5.0YS,Microchip Technology,576-1254-ND,digikey,1.4,SOT223,V_REG_317SMD,U2 U3
78,1,744710215 (DNP),Wurth Electronics Inc,732-3252-ND,digikey,1.9,ROD-CORE-CHOKE,DNP,U$12
79,2,39281083 (DNP),Molex LLC,WM3803-ND,digikey,1.3,CON-MOLEX_5566-8,DNP,X1 X2
80,1,ST3215SB32768E0HPWBB,AVX Corp/Kyocera Corp,1253-1335-1-ND,digikey,0.66,CRYSTAL-SMD-3.2X1.5MM,32.768kHz,Y2

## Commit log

2017-09-05 initital commit
2017-09-05 removing html from master
2017-09-05 renamed html file
2017-09-05 removing improper named file
2017-09-05 updated html file
2017-09-05 added sim files
2017-09-05 added noted to 2-axis control code
2017-09-05 updated videos
2017-09-06 removing DS_store
2017-09-06 added google analytics
2017-09-07 moved analytics script
2017-09-07 trying different form of analytics snippet
2017-09-07 fixed type
2017-09-07 reverted to old analytics snippet
2017-09-15 added configs
2017-12-31 added wheel part
2017-12-31 added step version of part
2018-01-06 added cad file
2018-01-06 adding kicad
2018-01-06 removed duplicated files
2018-01-06 removed kicad default library from this repo
2018-01-06 adding wheel drawing
2018-01-06 adding drawing
2018-01-07 adding wheel cad and gcode files
2018-01-07 adding correct drawing
2018-01-15 added bom csv
2018-01-15 updated PCB and created schematic pdf
2018-01-21 added schottkys to charging circuit
2018-01-25 added gerber and drill files
2018-01-27 added bom and updated board
2018-02-01 moved interfering resistor
2018-04-29 basic refactor complete, added *.zip to gitignore, removed outdated files
2018-04-29 added parametric plotting
2018-04-29 added pendulum class
2018-04-30 small mods
2018-06-05 saving latex progress
2018-07-12 got write up to a deceent state
2018-07-12 fixed path to images
2018-07-12 changed image sizes
2018-07-12 rearranged images
2018-07-12 increased rendering image display size
2018-07-12 fixed typo in rendering html
2018-07-12 increased rendering size
